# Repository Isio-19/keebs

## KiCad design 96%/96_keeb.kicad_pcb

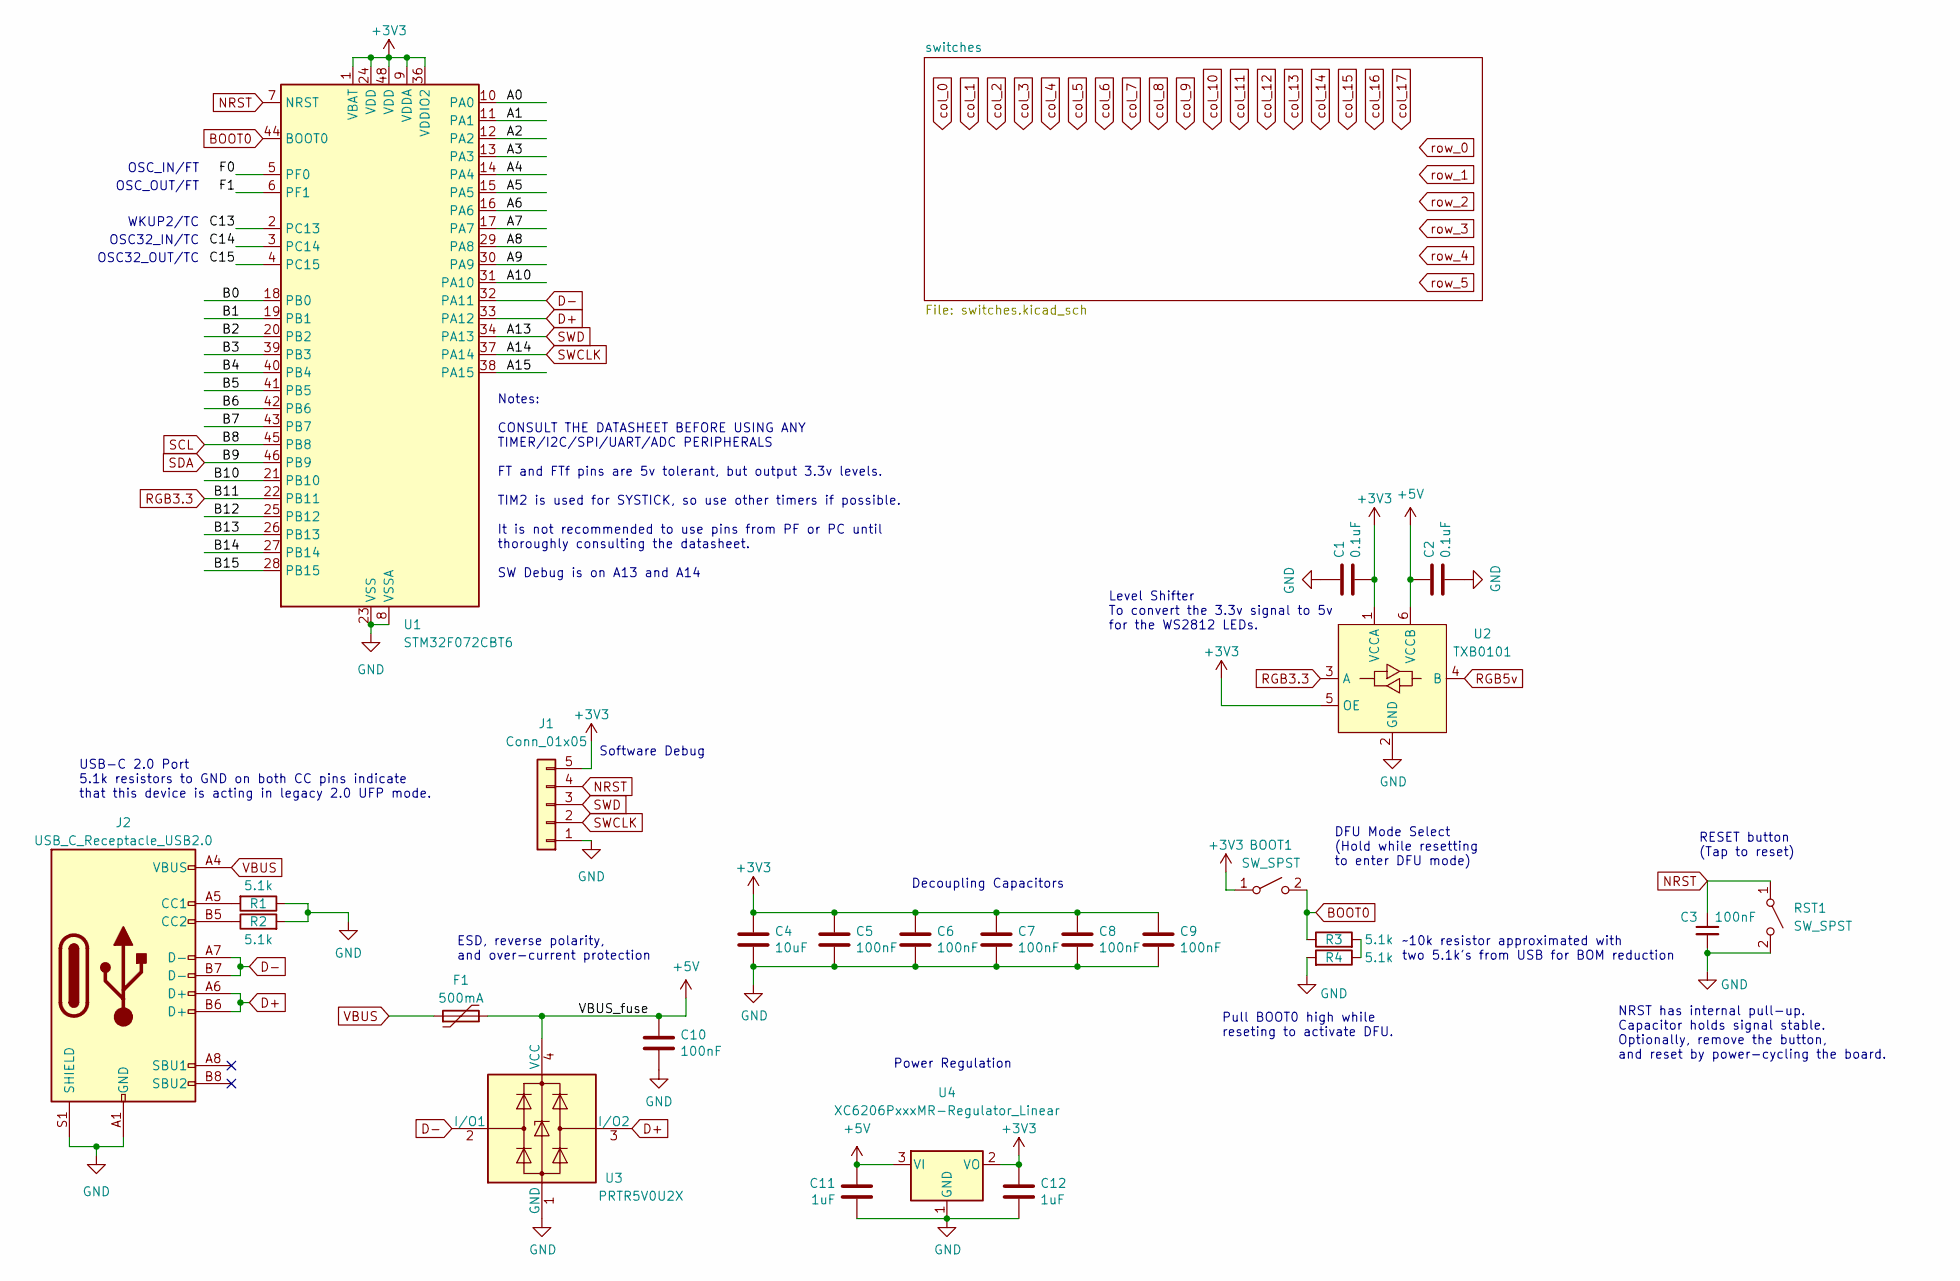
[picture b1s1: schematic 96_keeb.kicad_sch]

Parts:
BOOT1: SW_SPST; SW_SPST_TL3342
C1, C2: 0.1uF; C_0402_1005Metric; LCSC C307331
C3, C5, C6, C7, C8, C9, C10: 100nF; C_0402_1005Metric; LCSC C307331
C4: 10uF; C_0603_1608Metric; LCSC C307331
C11, C12: 1uF; C_0402_1005Metric; LCSC C307331
F1: 500mA; Fuse_1206_3216Metric; LCSC C135341
J1: Conn_01x05; PinHeader_1x05_P2.54mm_Vertical
J2: USB_C_Receptacle_USB2.0; USB_C_Receptacle_HRO_TYPE-C-31-M-12; JlcRotOffset 180
R1, R2, R3, R4: 5.1k; R_0402_1005Metric
RST1: SW_SPST; SW_SPST_TL3342
U1: STM32F072CBT6; LQFP-48_7x7mm_P0.5mm; JlcRotOffset 90
U2: TXB0101; SOT-363_SC-70-6; LCSC C324081
U3: PRTR5V0U2X; SOT-143; LCSC C2827688
U4: XC6206PxxxMR-Regulator_Linear; SOT-23; LCSC C5446

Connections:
+3V3: BOOT1.1 (A), C1.2, C4.1, C5.1, C6.1, C7.1, C8.1, C9.1, C12.1, J1.5, U1.1 (VBAT), U1.9 (VDDA), U1.24 (VDD), U1.36 (VDDIO2), U1.48 (VDD), U2.1 (VCCA), U2.5 (OE), U4.2 (VO)
+5V: C2.1, C10.1, C11.1, F1.2, U2.6 (VCCB), U3.4 (VCC), U4.3 (VI)
/A0: U1.10 (PA0)
/A1: U1.11 (PA1)
/A2: U1.12 (PA2)
/A3: U1.13 (PA3)
/A4: U1.14 (PA4)
/A5: U1.15 (PA5)
/A6: U1.16 (PA6)
/A7: U1.17 (PA7)
/A8: U1.29 (PA8)
/A9: U1.30 (PA9)
/A10: U1.31 (PA10)
/A15: U1.38 (PA15)
/B0: U1.18 (PB0)
/B1: U1.19 (PB1)
/B2: U1.20 (PB2)
/B3: U1.39 (PB3)
/B4: U1.40 (PB4)
/B5: U1.41 (PB5)
/B6: U1.42 (PB6)
/B7: U1.43 (PB7)
/B10: U1.21 (PB10)
/B12: U1.25 (PB12)
/B13: U1.26 (PB13)
/B14: U1.27 (PB14)
/B15: U1.28 (PB15)
/C13: U1.2 (PC13)
/C14: U1.3 (PC14)
/C15: U1.4 (PC15)
/F0: U1.5 (PF0)
/F1: U1.6 (PF1)
BOOT0: BOOT1.2 (B), R3.1, U1.44 (BOOT0)
D+: J2.A6 (D+), J2.B6 (D+), U1.33 (PA12), U3.3 (I/O2)
D-: J2.A7 (D-), J2.B7 (D-), U1.32 (PA11), U3.2 (I/O1)
GND: C1.1, C2.2, C3.2, C4.2, C5.2, C6.2, C7.2, C8.2, C9.2, C10.2, C11.2, C12.2, J1.1, J2.A1 (GND), J2.A12 (GND), J2.B1 (GND), J2.B12 (GND), J2.S1 (SHIELD), R1.1, R2.2, R4.2, RST1.2 (B), U1.8 (VSSA), U1.23 (VSS), U1.35 (VSS), U1.47 (VSS), U2.2 (GND), U3.1 (GND), U4.1 (GND)
NRST: C3.1, J1.4, RST1.1 (A), U1.7 (NRST)
unnamed: J2.A5 (CC1), R1.2
unnamed: J2.B5 (CC2), R2.1
unnamed: R3.2, R4.1
RGB3.3: U1.22 (PB11), U2.3 (A)
RGB5v: U2.4 (B)
SCL: U1.45 (PB8)
SDA: U1.46 (PB9)
SWCLK: J1.2, U1.37 (PA14)
SWD: J1.3, U1.34 (PA13)
VBUS: F1.1, J2.A4 (VBUS), J2.A9 (VBUS), J2.B4 (VBUS), J2.B9 (VBUS)

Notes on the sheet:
Decoupling Capacitors
~10k resistor approximated with two 5.1k's from USB for BOM reduction
Notes: CONSULT THE DATASHEET BEFORE USING ANY TIMER/I2C/SPI/UART/ADC PERIPHERALS FT and FTf pins are 5v tolerant, but output 3.3v levels. TIM2 is used for SYSTICK, so use other timers if possible. It is not recommended to use pins from PF or PC until thoroughly consulting the datasheet. SW Debug is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
RESET button (Tap to reset)
Power Regulation
OSC_IN/FT
OSC32_OUT/TC
USB-C 2.0 Port 5.1k resistors to GND on both CC pins indicate that this device is acting in legacy 2.0 UFP mode.
WKUP2/TC
OSC_OUT/FT
ESD, reverse polarity, and over-current protection
Software Debug
NRST has internal pull-up. Capacitor holds signal stable. Optionally, remove the button, and reset by power-cycling the board.
OSC32_IN/TC
Pull BOOT0 high while reseting to activate DFU.
Level Shifter To convert the 3.3v signal to 5v for the WS2812 LEDs.
DFU Mode Select (Hold while resetting to enter DFU mode)

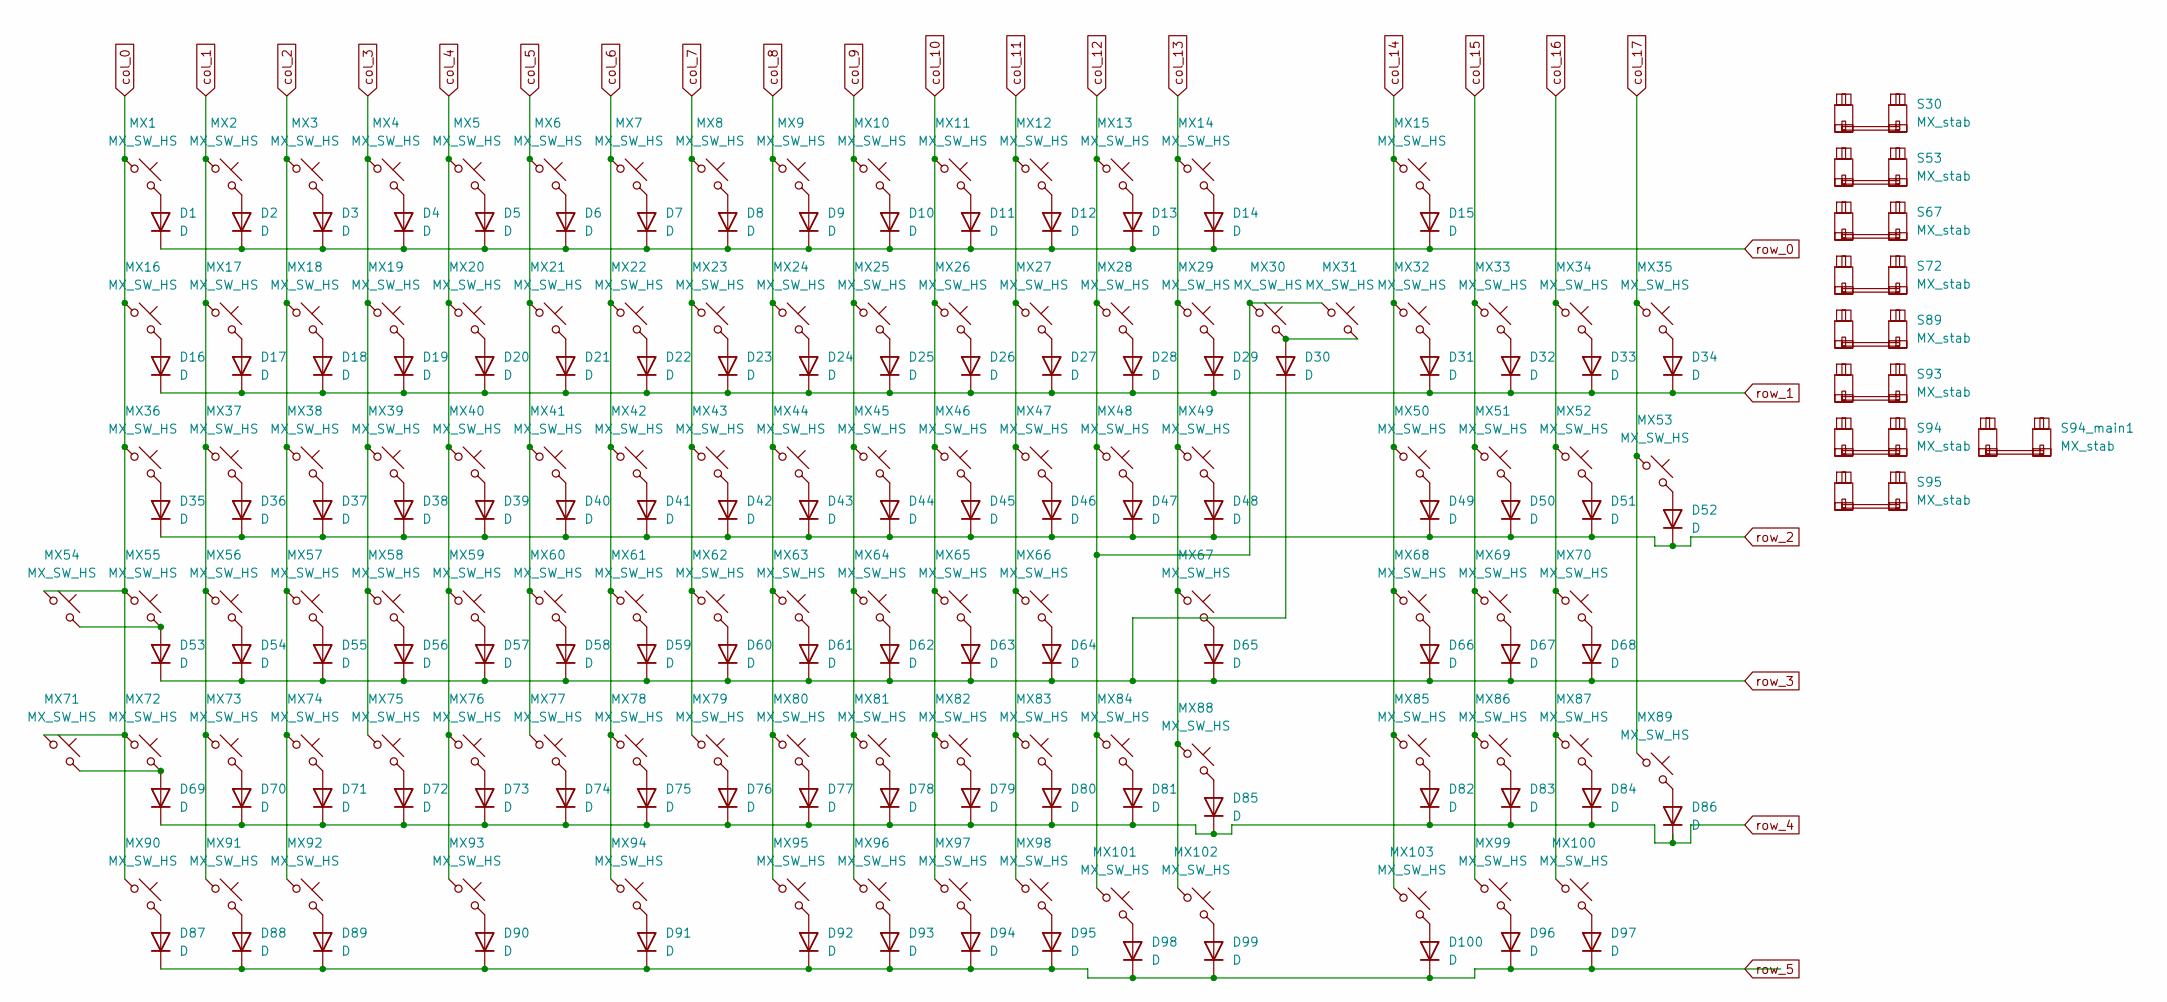
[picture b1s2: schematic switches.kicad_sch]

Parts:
D1, D2, D3, D4, D5, D6, D7, D8, D9, D10, D11, D12, D13, D14, D15, D16, D17, D18, D19, D20, D21, D22, D23, D24, D25, D26, D27, D28, D29, D30, D31, D32, D33, D34, D35, D36, D37, D38, D39, D40, D41, D42, D43, D44, D45, D46, D47, D48, D49, D50, D51, D52, D53, D54, D55, D56, D57, D58, D59, D60, D61, D62, D63, D64, D65, D66, D67, D68, D69, D70, D71, D72, D73, D74, D75, D76, D77, D78, D79, D80, D81, D82, D83, D84, D85, D86, D87, D88, D89, D90, D91, D92, D93, D94, D95, D96, D97, D98, D99, D100: D; D_SOD-123
MX1, MX2, MX3, MX4, MX5, MX6, MX7, MX8, MX9, MX10, MX11, MX12, MX13, MX14, MX15, MX16, MX17, MX18, MX19, MX20, MX21, MX22, MX23, MX24, MX25, MX26, MX27, MX28, MX29, MX30, MX31, MX32, MX33, MX34, MX35, MX36, MX37, MX38, MX39, MX40, MX41, MX42, MX43, MX44, MX45, MX46, MX47, MX48, MX49, MX50, MX51, MX52, MX53, MX54, MX55, MX56, MX57, MX58, MX59, MX60, MX61, MX62, MX63, MX64, MX65, MX66, MX67, MX68, MX69, MX70, MX71, MX72, MX73, MX74, MX75, MX76, MX77, MX78, MX79, MX80, MX81, MX82, MX83, MX84, MX85, MX86, MX87, MX88, MX89, MX90, MX91, MX92, MX93, MX94, MX95, MX96, MX97, MX98, MX99, MX100, MX101, MX102, MX103: MX_SW_HS; SW_MX_HS_CPG151101S11_1u
S30, S53, S67, S89, S93, S95: MX_stab; STAB_MX_P_2u
S72, S94: MX_stab; STAB_MX_P_2.25u
S94_main1: MX_stab; STAB_MX_P_6.25u

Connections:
unnamed: D1.2 (A), MX1.2
unnamed: D2.2 (A), MX2.2
unnamed: D3.2 (A), MX3.2
unnamed: D4.2 (A), MX4.2
unnamed: D5.2 (A), MX5.2
unnamed: D6.2 (A), MX6.2
unnamed: D7.2 (A), MX7.2
unnamed: D8.2 (A), MX8.2
unnamed: D9.2 (A), MX9.2
unnamed: D10.2 (A), MX10.2
unnamed: D11.2 (A), MX11.2
unnamed: D12.2 (A), MX12.2
unnamed: D13.2 (A), MX13.2
unnamed: D14.2 (A), MX14.2
unnamed: D15.2 (A), MX15.2
unnamed: D16.2 (A), MX16.2
unnamed: D17.2 (A), MX17.2
unnamed: D18.2 (A), MX18.2
unnamed: D19.2 (A), MX19.2
unnamed: D20.2 (A), MX20.2
unnamed: D21.2 (A), MX21.2
unnamed: D22.2 (A), MX22.2
unnamed: D23.2 (A), MX23.2
unnamed: D24.2 (A), MX24.2
unnamed: D25.2 (A), MX25.2
unnamed: D26.2 (A), MX26.2
unnamed: D27.2 (A), MX27.2
unnamed: D28.2 (A), MX28.2
unnamed: D29.2 (A), MX29.2
unnamed: D30.2 (A), MX30.2, MX31.2
unnamed: D31.2 (A), MX32.2
unnamed: D32.2 (A), MX33.2
unnamed: D33.2 (A), MX34.2
unnamed: D34.2 (A), MX35.2
unnamed: D35.2 (A), MX36.2
unnamed: D36.2 (A), MX37.2
unnamed: D37.2 (A), MX38.2
unnamed: D38.2 (A), MX39.2
unnamed: D39.2 (A), MX40.2
unnamed: D40.2 (A), MX41.2
unnamed: D41.2 (A), MX42.2
unnamed: D42.2 (A), MX43.2
unnamed: D43.2 (A), MX44.2
unnamed: D44.2 (A), MX45.2
unnamed: D45.2 (A), MX46.2
unnamed: D46.2 (A), MX47.2
unnamed: D47.2 (A), MX48.2
unnamed: D48.2 (A), MX49.2
unnamed: D49.2 (A), MX50.2
unnamed: D50.2 (A), MX51.2
unnamed: D51.2 (A), MX52.2
unnamed: D52.2 (A), MX53.2
unnamed: D53.2 (A), MX54.2, MX55.2
unnamed: D54.2 (A), MX56.2
unnamed: D55.2 (A), MX57.2
unnamed: D56.2 (A), MX58.2
unnamed: D57.2 (A), MX59.2
unnamed: D58.2 (A), MX60.2
unnamed: D59.2 (A), MX61.2
unnamed: D60.2 (A), MX62.2
unnamed: D61.2 (A), MX63.2
unnamed: D62.2 (A), MX64.2
unnamed: D63.2 (A), MX65.2
unnamed: D64.2 (A), MX66.2
unnamed: D65.2 (A), MX67.2
unnamed: D66.2 (A), MX68.2
unnamed: D67.2 (A), MX69.2
unnamed: D68.2 (A), MX70.2
unnamed: D69.2 (A), MX71.2, MX72.2
unnamed: D70.2 (A), MX73.2
unnamed: D71.2 (A), MX74.2
unnamed: D72.2 (A), MX75.2
unnamed: D73.2 (A), MX76.2
unnamed: D74.2 (A), MX77.2
unnamed: D75.2 (A), MX78.2
unnamed: D76.2 (A), MX79.2
unnamed: D77.2 (A), MX80.2
unnamed: D78.2 (A), MX81.2
unnamed: D79.2 (A), MX82.2
unnamed: D80.2 (A), MX83.2
unnamed: D81.2 (A), MX84.2
unnamed: D82.2 (A), MX85.2
unnamed: D83.2 (A), MX86.2
unnamed: D84.2 (A), MX87.2
unnamed: D85.2 (A), MX88.2
unnamed: D86.2 (A), MX89.2
unnamed: D87.2 (A), MX90.2
unnamed: D88.2 (A), MX91.2
unnamed: D89.2 (A), MX92.2
unnamed: D90.2 (A), MX93.2
unnamed: D91.2 (A), MX94.2
unnamed: D92.2 (A), MX95.2
unnamed: D93.2 (A), MX96.2
unnamed: D94.2 (A), MX97.2
unnamed: D95.2 (A), MX98.2
unnamed: D96.2 (A), MX99.2
unnamed: D97.2 (A), MX100.2
unnamed: D98.2 (A), MX101.2
unnamed: D99.2 (A), MX102.2
unnamed: D100.2 (A), MX103.2
col_0: MX1.1, MX16.1, MX36.1, MX54.1, MX55.1, MX71.1, MX72.1, MX90.1
col_1: MX2.1, MX17.1, MX37.1, MX56.1, MX73.1, MX91.1
col_2: MX3.1, MX18.1, MX38.1, MX57.1, MX74.1, MX92.1
col_3: MX4.1, MX19.1, MX39.1, MX58.1, MX75.1
col_4: MX5.1, MX20.1, MX40.1, MX59.1, MX76.1, MX93.1
col_5: MX6.1, MX21.1, MX41.1, MX60.1, MX77.1
col_6: MX7.1, MX22.1, MX42.1, MX61.1, MX78.1, MX94.1
col_7: MX8.1, MX23.1, MX43.1, MX62.1, MX79.1
col_8: MX9.1, MX24.1, MX44.1, MX63.1, MX80.1, MX95.1
col_9: MX10.1, MX25.1, MX45.1, MX64.1, MX81.1, MX96.1
col_10: MX11.1, MX26.1, MX46.1, MX65.1, MX82.1, MX97.1
col_11: MX12.1, MX27.1, MX47.1, MX66.1, MX83.1, MX98.1
col_12: MX13.1, MX28.1, MX30.1, MX31.1, MX48.1, MX84.1, MX101.1
col_13: MX14.1, MX29.1, MX49.1, MX67.1, MX88.1, MX102.1
col_14: MX15.1, MX32.1, MX50.1, MX68.1, MX85.1, MX103.1
col_15: MX33.1, MX51.1, MX69.1, MX86.1, MX99.1
col_16: MX34.1, MX52.1, MX70.1, MX87.1, MX100.1
col_17: MX35.1, MX53.1, MX89.1
row_0: D1.1 (K), D2.1 (K), D3.1 (K), D4.1 (K), D5.1 (K), D6.1 (K), D7.1 (K), D8.1 (K), D9.1 (K), D10.1 (K), D11.1 (K), D12.1 (K), D13.1 (K), D14.1 (K), D15.1 (K)
row_1: D16.1 (K), D17.1 (K), D18.1 (K), D19.1 (K), D20.1 (K), D21.1 (K), D22.1 (K), D23.1 (K), D24.1 (K), D25.1 (K), D26.1 (K), D27.1 (K), D28.1 (K), D29.1 (K), D31.1 (K), D32.1 (K), D33.1 (K), D34.1 (K)
row_2: D35.1 (K), D36.1 (K), D37.1 (K), D38.1 (K), D39.1 (K), D40.1 (K), D41.1 (K), D42.1 (K), D43.1 (K), D44.1 (K), D45.1 (K), D46.1 (K), D47.1 (K), D48.1 (K), D49.1 (K), D50.1 (K), D51.1 (K), D52.1 (K)
row_3: D30.1 (K), D53.1 (K), D54.1 (K), D55.1 (K), D56.1 (K), D57.1 (K), D58.1 (K), D59.1 (K), D60.1 (K), D61.1 (K), D62.1 (K), D63.1 (K), D64.1 (K), D65.1 (K), D66.1 (K), D67.1 (K), D68.1 (K)
row_4: D69.1 (K), D70.1 (K), D71.1 (K), D72.1 (K), D73.1 (K), D74.1 (K), D75.1 (K), D76.1 (K), D77.1 (K), D78.1 (K), D79.1 (K), D80.1 (K), D81.1 (K), D82.1 (K), D83.1 (K), D84.1 (K), D85.1 (K), D86.1 (K)
row_5: D87.1 (K), D88.1 (K), D89.1 (K), D90.1 (K), D91.1 (K), D92.1 (K), D93.1 (K), D94.1 (K), D95.1 (K), D96.1 (K), D97.1 (K), D98.1 (K), D99.1 (K), D100.1 (K)

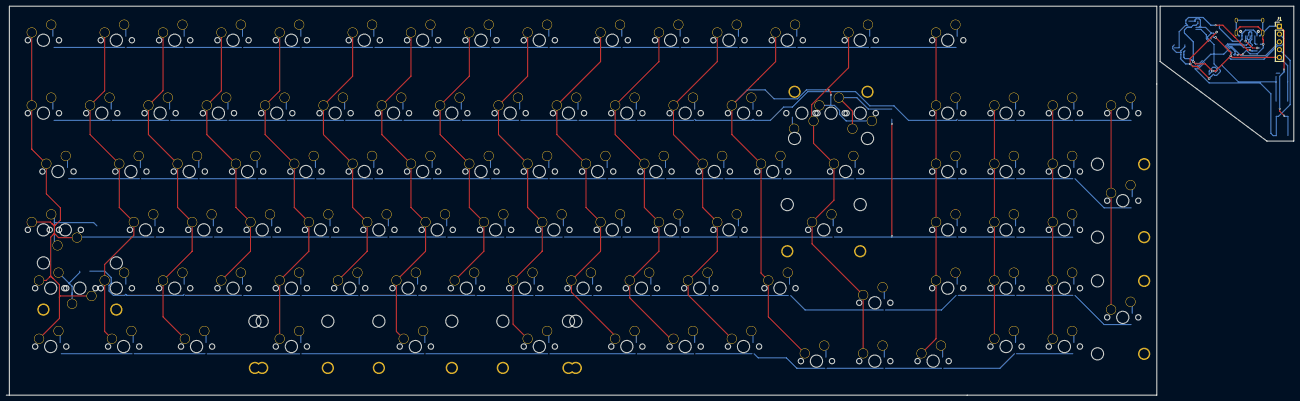
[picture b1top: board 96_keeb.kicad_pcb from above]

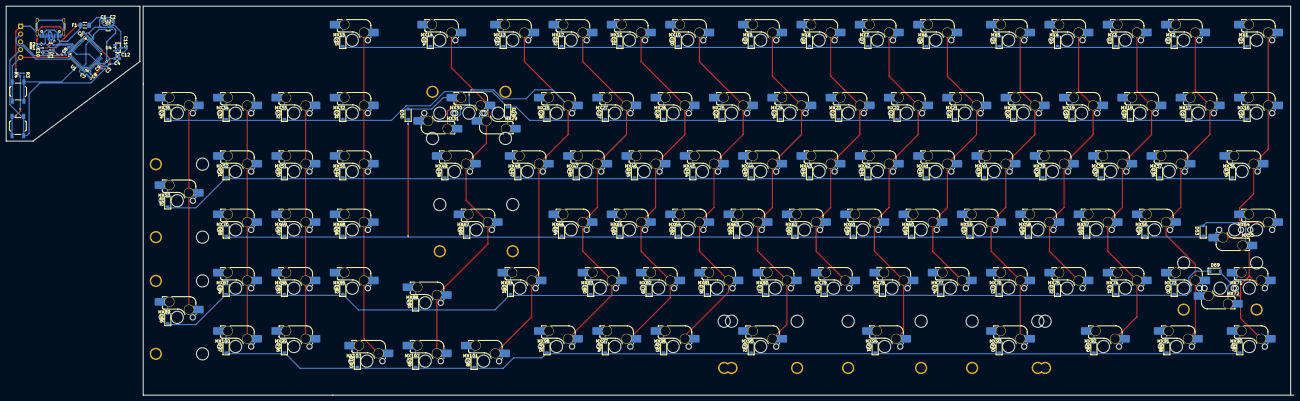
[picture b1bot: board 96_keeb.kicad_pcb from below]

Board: 2 copper layers, 420.4 x 127.0 mm, 237 parts (236 on the bottom side), 138 nets.

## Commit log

2026-02-26 Added switch schematic
2026-02-26 Added global labels to main schematic
2026-02-26 Assigned footprints to diodes
2026-02-26 PCB switch placement
2026-02-26 Switch wire routing
2026-02-26 Alternative layout wiring
2026-03-05 Added 96% alt layout wiring
2026-03-16 LED wiring for 96% layout
2026-03-18 Finished LEDs wirign
2026-03-27 Finished wiring on 96% keyboard
2026-03-29 Finished wiring 96% layout
